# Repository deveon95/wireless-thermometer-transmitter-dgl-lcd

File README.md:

# wireless-thermometer-transmitter-dgl-lcd
PIC firmware and PCB layout for wireless 433MHz temperature transmitter

See [my blog](https://blog.schollar.uk/2025/09/more-wireless-temperature-displays-low.html) for more details about this project.

Integrates with various display devices I've made which share this protocol, including but not limited to [wireless-thermometer-display-esp32](https://github.com/deveon95/wireless-thermometer-display-esp32). The data format is also compatible with the rfin command on PICAXE microcontrollers.

The PCB is designed to fit in the same space as 3xAA cells so that a battery box can be modified to house it. If using a 4xAA battery box, this leaves room for only one cell so a LiFePO4 cell is ideal in that case.

The LCD is a DGL-0401YG-4EH bare glass LCD with backlight. The backlight is wired in a 2 in series x 2 in parallel configuration; the backlight should be carefully removed, and re-wired with a scalpel and enamel wire with all four LEDs in parallel if it is to light on a 3V battery.

Button functions at temperature screen:

* Left - enter menu
* Right - backlight

Button functions inside menu:

* Left - next item
* Right - enter / increment current item (decrement current item if left button is held down)

Menu settings:

* CON - contrast
* LAT - LRLAT (LCD Reference Ladder A Time Interval Control bits)
* TH - number of thermistors connected (1 or 2)
* ID - unique ID of the thermistor in the system
* CAL - calibration

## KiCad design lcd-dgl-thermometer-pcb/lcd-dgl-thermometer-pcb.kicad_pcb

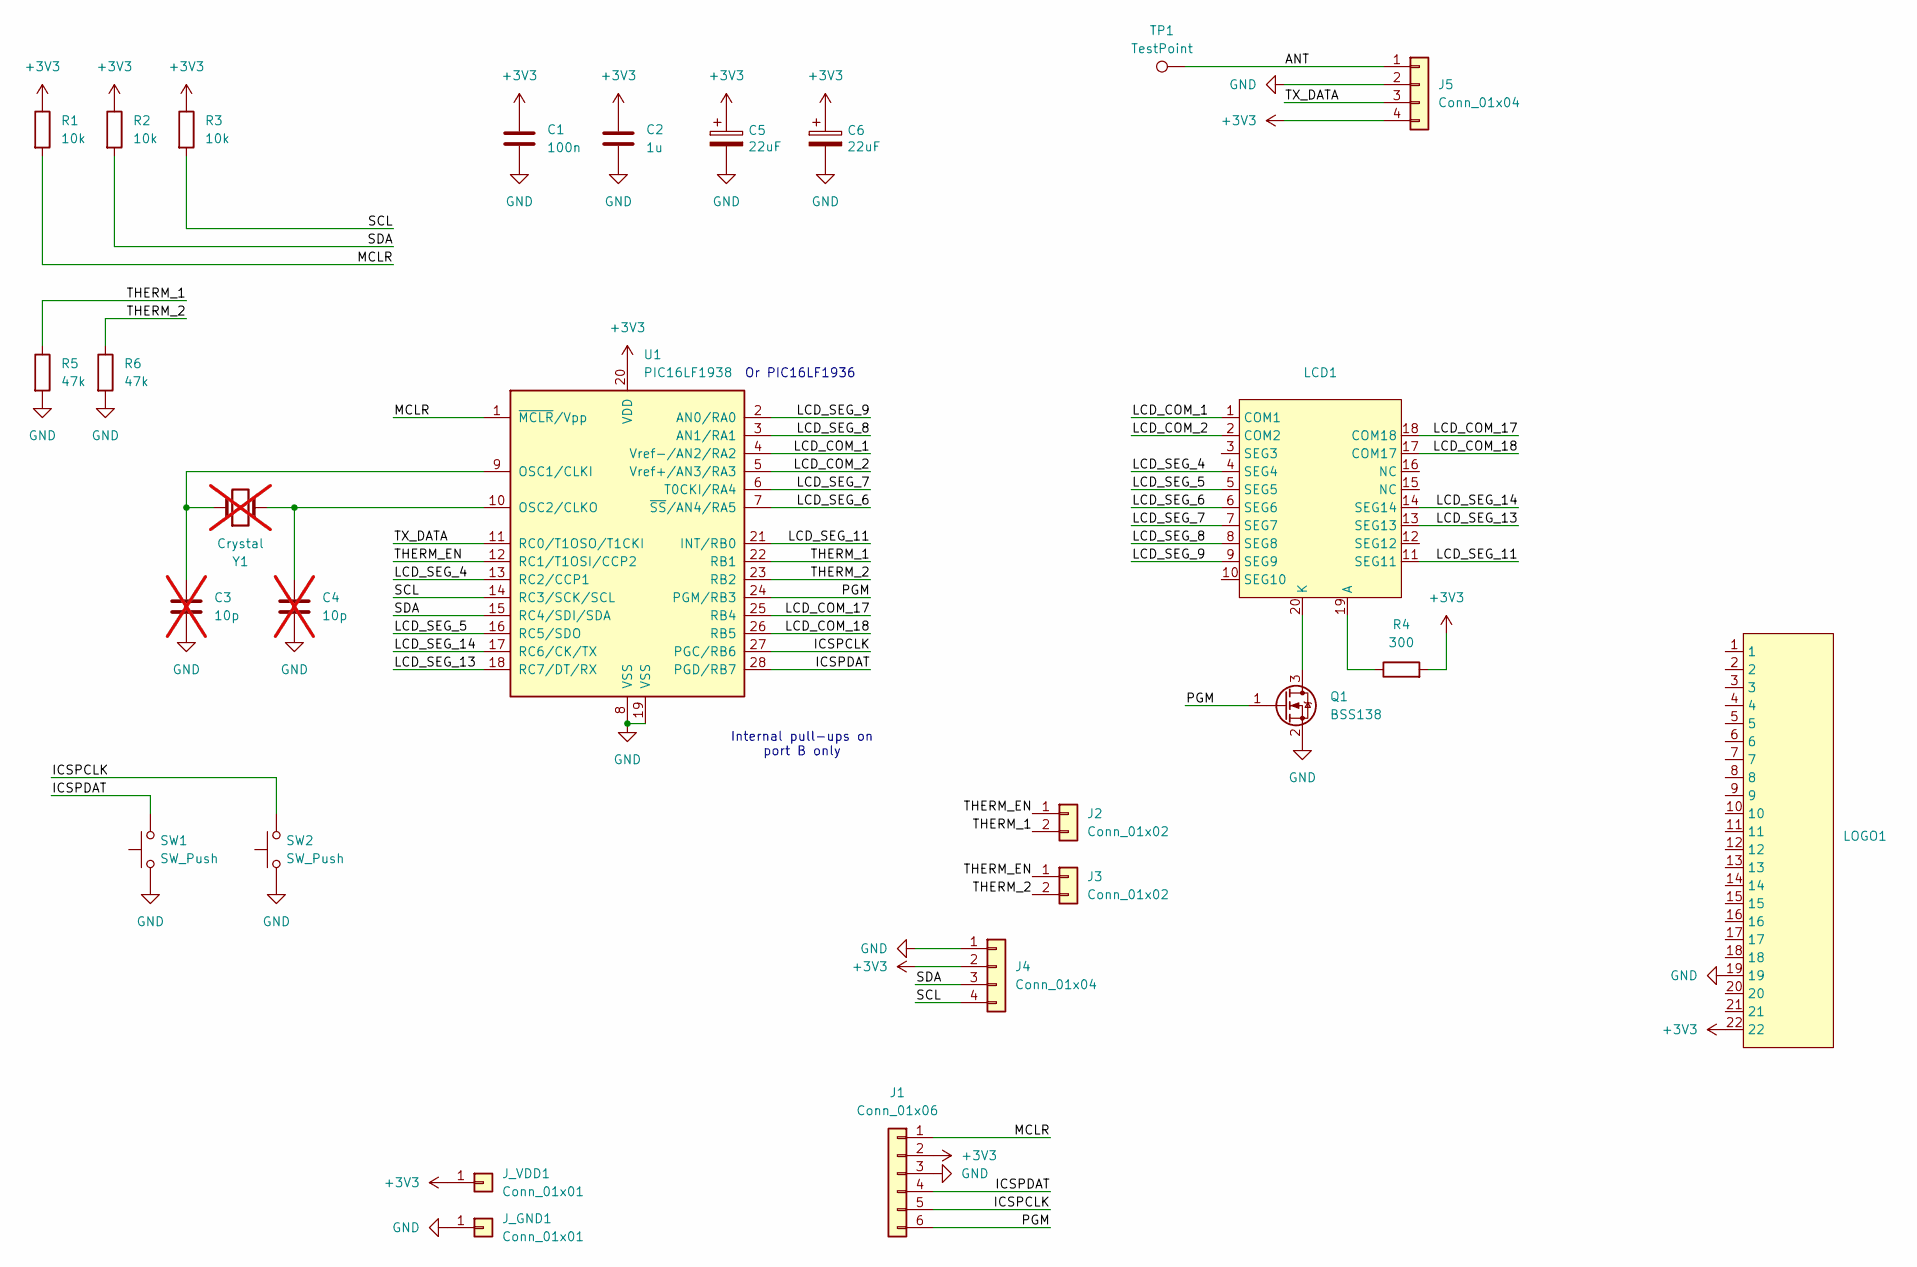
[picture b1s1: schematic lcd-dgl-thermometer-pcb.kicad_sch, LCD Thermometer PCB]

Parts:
C1: 100n; C_0603_1608Metric
C2: 1u; C_0603_1608Metric
C3, C4: 10p; C_0603_1608Metric; not fitted
C5, C6: 22uF; CP_Elec_6.3x5.4
J1: Conn_01x06; PinHeader_1x06_P2.54mm_Vertical
J2, J3: Conn_01x02; PinHeader_1x02_P2.54mm_Vertical
J4: Conn_01x04; JST_SH_SM04B-SRSS-TB_1x04-1MP_P1.00mm_Horizontal
J5: Conn_01x04; PinHeader_1x04_P2.54mm_Vertical
J_GND1: Conn_01x01; SolderWire-1sqmm_1x01_D1.4mm_OD2.7mm
J_VDD1: Conn_01x01; SolderWire-1sqmm_1x01_D1.4mm_OD2.7mm
LCD1: Kemo_2_4_DGL_Three_Digit_LCD_Edge_BL
LOGO1: LCD_DGL_Space_Filler
Q1: BSS138; SOT-23
R1, R2, R3: 10k; R_0603_1608Metric
R4: 300; R_0603_1608Metric
R5, R6: 47k; R_0603_1608Metric
SW1, SW2: SW_Push; SW_PUSH_1P1T_6x3.5mm_H4.3_APEM_MJTP1243
TP1: TestPoint; TestPoint_Pad_1.5x1.5mm
U1: PIC16LF1938; SOIC-28W_7.5x17.9mm_P1.27mm
Y1: Crystal; Crystal_SMD_HC49-SD; not fitted

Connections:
+3V3: C1.1, C2.1, C5.1, C6.1, J1.2, J4.2, J5.4, J_VDD1.1, LOGO1.22, R1.1, R2.1, R3.1, R4.2, U1.20 (VDD)
/ANT: J5.1, TP1.1
/ICSPCLK: J1.5, SW2.2, U1.27 (PGC/RB6)
/ICSPDAT: J1.4, SW1.2, U1.28 (PGD/RB7)
/LCD_COM_1: LCD1.1 (COM1), U1.4 (Vref-/AN2/RA2)
/LCD_COM_2: LCD1.2 (COM2), U1.5 (Vref+/AN3/RA3)
/LCD_COM_17: LCD1.18 (COM18), U1.25 (RB4)
/LCD_COM_18: LCD1.17 (COM17), U1.26 (RB5)
/LCD_SEG_4: LCD1.4 (SEG4), U1.13 (RC2/CCP1)
/LCD_SEG_5: LCD1.5 (SEG5), U1.16 (RC5/SDO)
/LCD_SEG_6: LCD1.6 (SEG6), U1.7 (~SS/AN4/RA5)
/LCD_SEG_7: LCD1.7 (SEG7), U1.6 (T0CKI/RA4)
/LCD_SEG_8: LCD1.8 (SEG8), U1.3 (AN1/RA1)
/LCD_SEG_9: LCD1.9 (SEG9), U1.2 (AN0/RA0)
/LCD_SEG_11: LCD1.11 (SEG11), U1.21 (INT/RB0)
/LCD_SEG_13: LCD1.13 (SEG13), U1.18 (RC7/DT/RX)
/LCD_SEG_14: LCD1.14 (SEG14), U1.17 (RC6/CK/TX)
/MCLR: J1.1, R1.2, U1.1 (~MCLR/Vpp)
/PGM: J1.6, Q1.1 (G), U1.24 (PGM/RB3)
/SCL: J4.4, R3.2, U1.14 (RC3/SCK/SCL)
/SDA: J4.3, R2.2, U1.15 (RC4/SDI/SDA)
/THERM_1: J2.2, R5.1, U1.22 (RB1)
/THERM_2: J3.2, R6.1, U1.23 (RB2)
/THERM_EN: J2.1, J3.1, U1.12 (RC1/T1OSI/CCP2)
/TX_DATA: J5.3, U1.11 (RC0/T1OSO/T1CKI)
GND: C1.2, C2.2, C3.2, C4.2, C5.2, C6.2, J1.3, J4.1, J5.2, J_GND1.1, LOGO1.19, Q1.2 (S), R5.2, R6.2, SW1.1, SW2.1, U1.8 (VSS), U1.19 (VSS)
unnamed: LCD1.19 (A), R4.1
unnamed: LCD1.20 (K), Q1.3 (D)
unnamed: C3.1, U1.9 (OSC1/CLKI), Y1.1
unnamed: C4.1, U1.10 (OSC2/CLKO), Y1.2

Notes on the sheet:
Or PIC16LF1936
Internal pull-ups on port B only

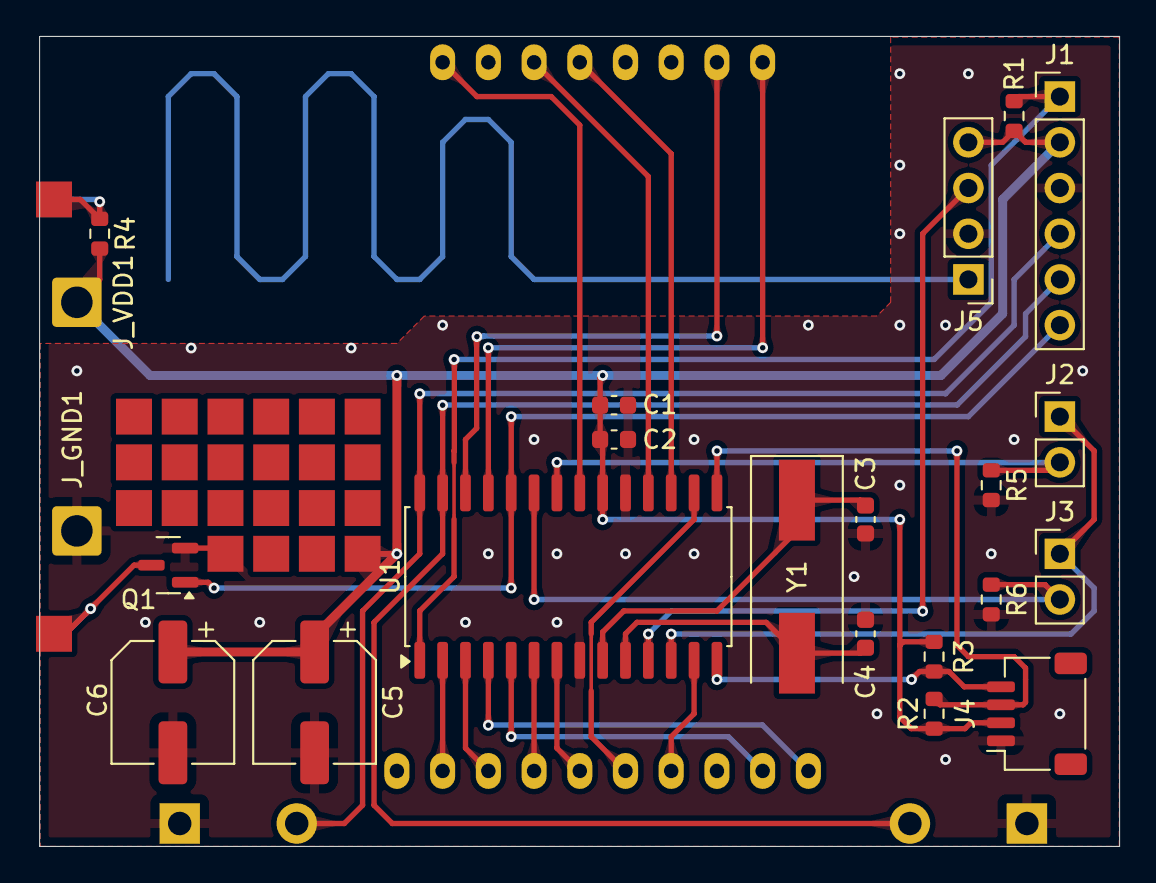
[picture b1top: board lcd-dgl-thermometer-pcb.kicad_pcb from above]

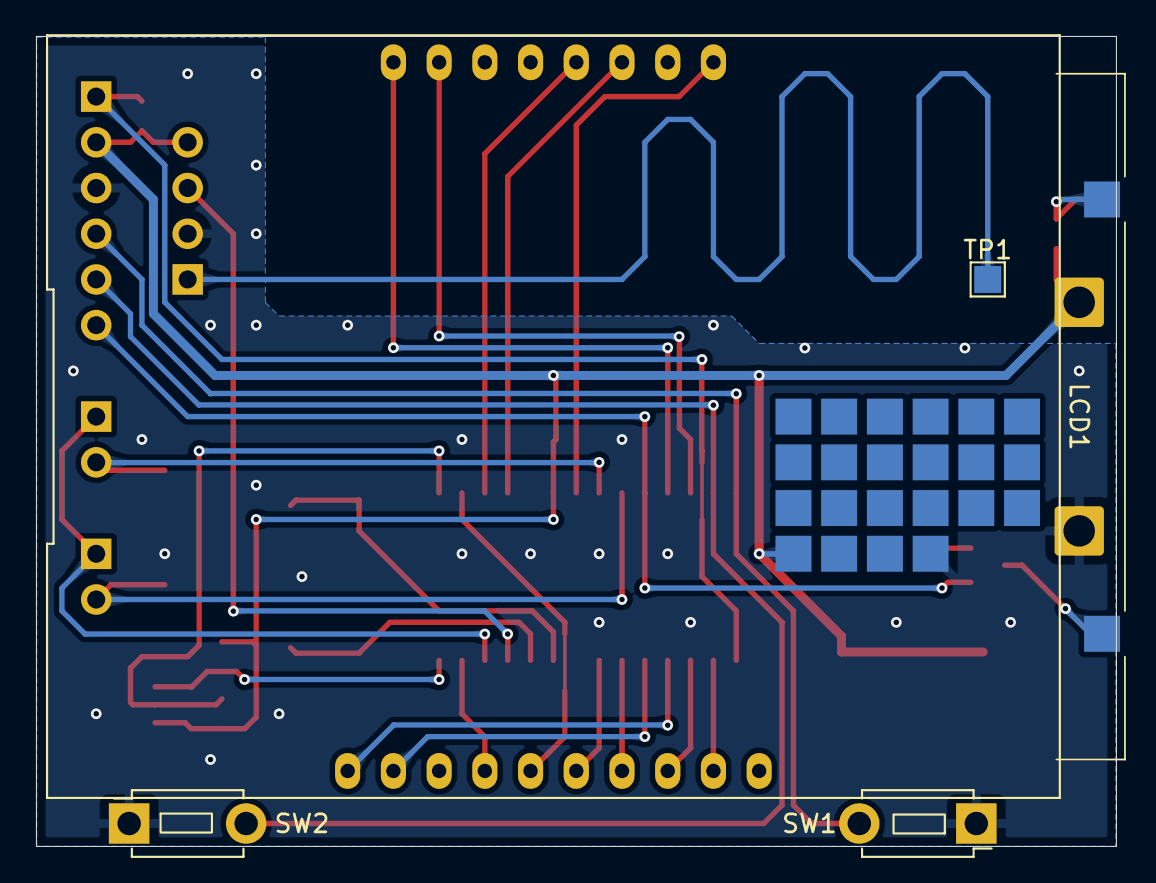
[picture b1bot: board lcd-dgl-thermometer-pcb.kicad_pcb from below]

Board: 2 copper layers, 60.0 x 45.0 mm, 27 parts (4 on the bottom side), 30 nets.

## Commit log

2025-08-25 Add information about the LCD
2025-08-25 Add info about buttons
2025-08-25 CHange URL
2025-09-20 Add link to blog
